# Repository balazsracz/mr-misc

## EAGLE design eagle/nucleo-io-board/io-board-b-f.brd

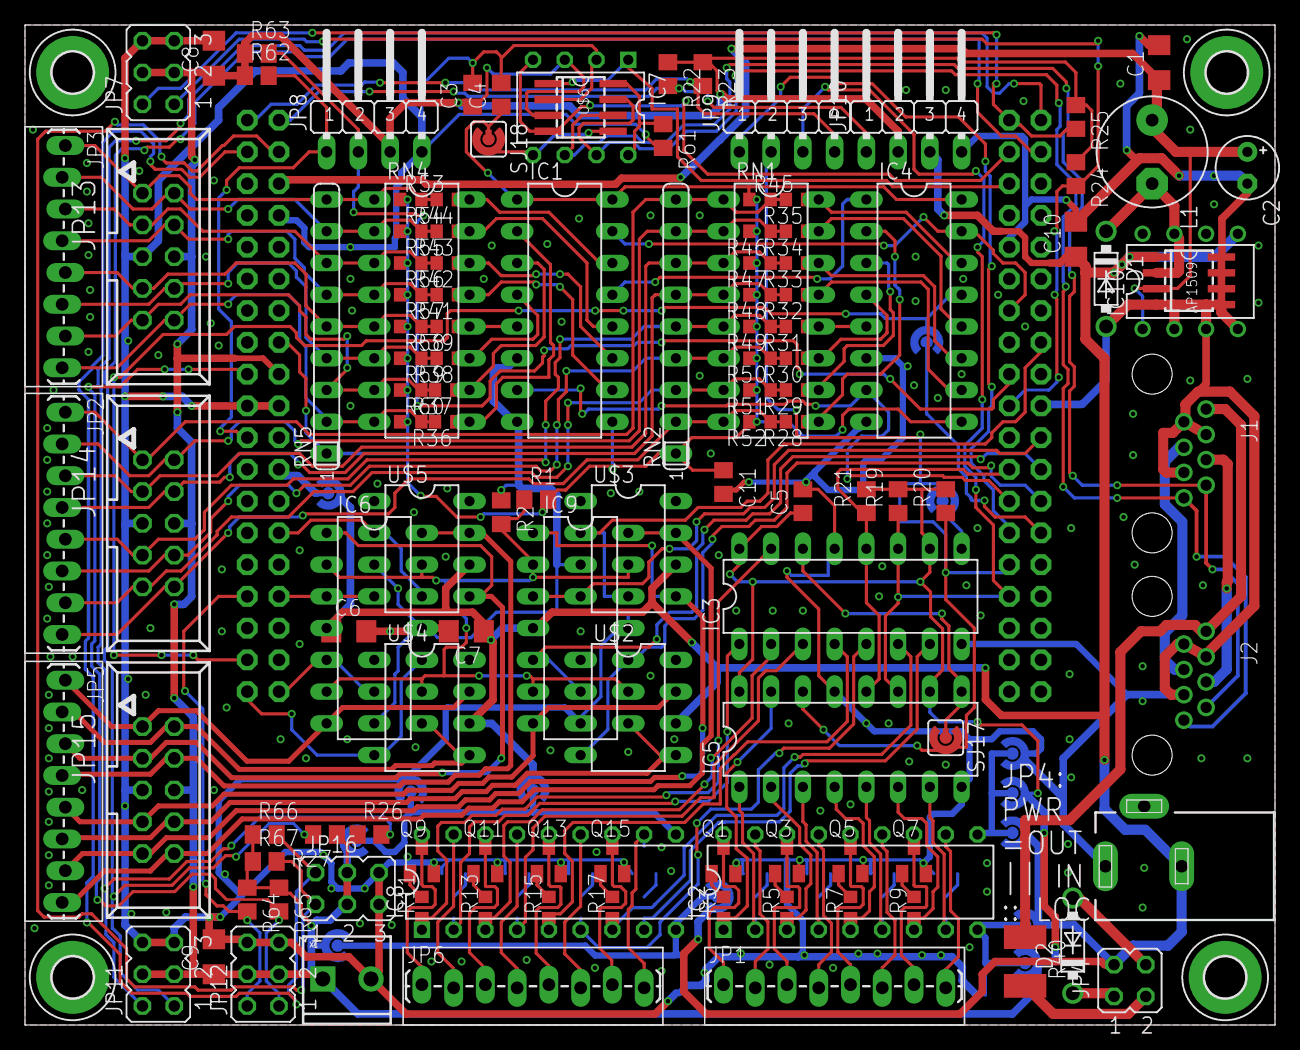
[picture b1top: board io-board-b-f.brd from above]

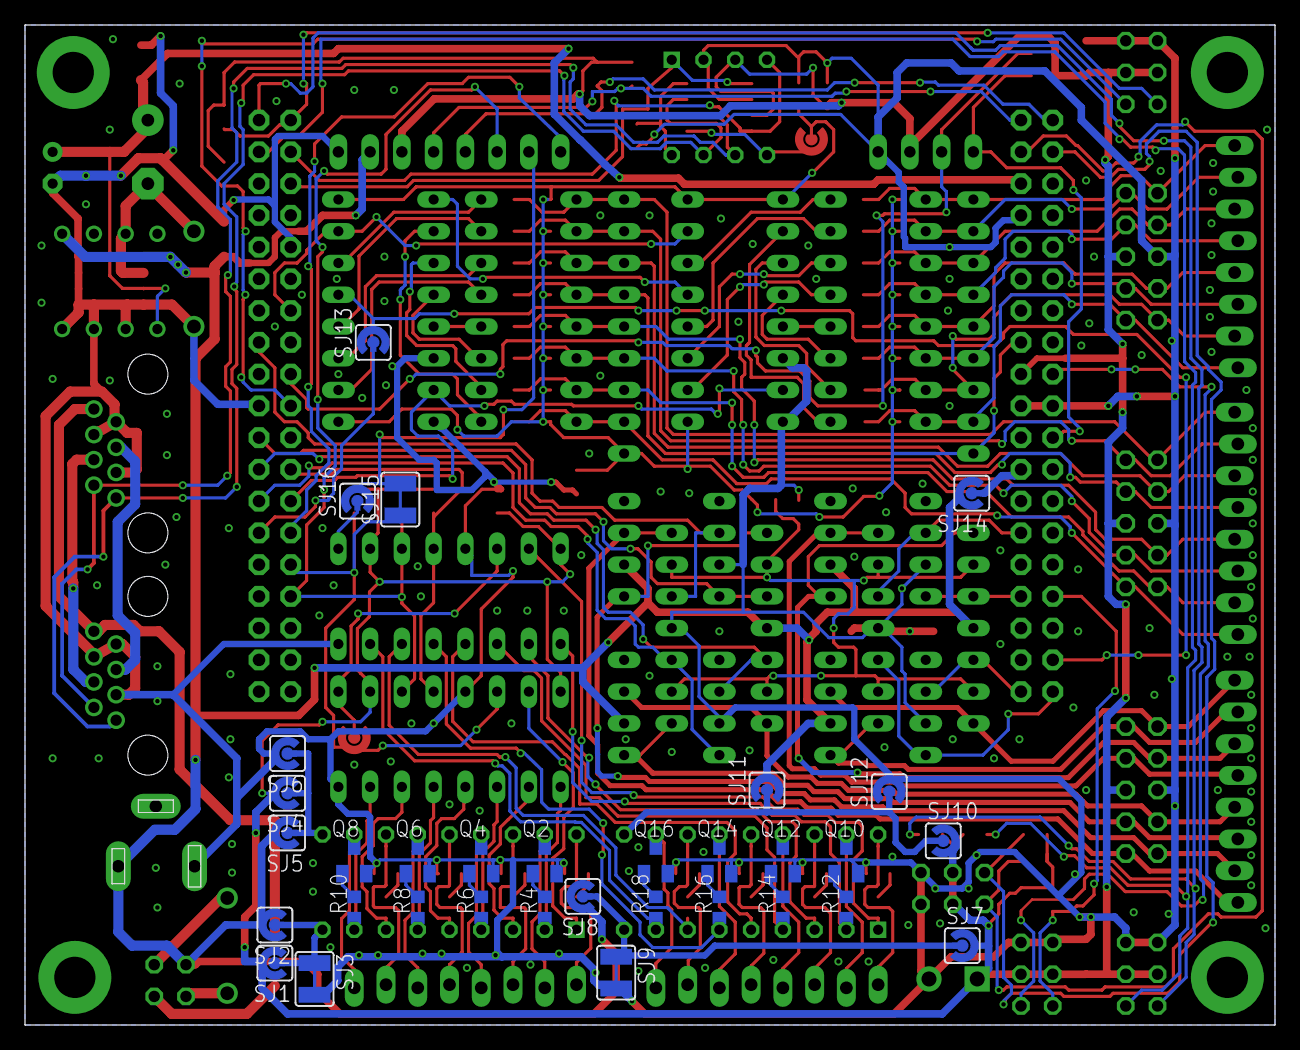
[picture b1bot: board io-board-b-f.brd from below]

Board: 2 copper layers, 100.0 x 80.0 mm, 161 parts (32 on the bottom side), 144 nets.

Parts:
+12V: 9-15V; POWER_USAGE
AP1509: AP1509; SO-08
C1, C6, C7, C8, C9, C10: C1206
C2: E2,5-5
C3, C4, C5, C11: C0805
D1, D2: DO41-7.6
H1, H2, H3, H4: MOUNT-PAD-ROUND3.3; 3,3-PAD
IC1, IC4: 74166N; DIL16
IC2, IC8: DIL18-THIN
IC3, IC5: 74HCT595N; DIL16
IC6, IC9: LM324N; DIL14
IC7: PCA82C250; DIL08
IC10: LM2574N-5.0; DIL08
J1, J2: RJ45-JACKRJ45-PULSE-E5J00; RJ45-PULSE-E5J88
J3: DCJ0202
JP1, JP2, JP3, JP5, JP6: M08-SCREW; 1X08_TERMINAL
JP4: JP2Q
JP7, JP11, JP12, JP16: JP3Q
JP8, JP9, JP10: JP4F
JP13, JP14, JP15: CON10M
L1: L-US; L5-8,5
Q1, Q2, Q3, Q4, Q5, Q6, Q7, Q8, Q9, Q10, Q11, Q12, Q13, Q14, Q15, Q16: SOT23
R1, R2: 10k; R0805
R3, R4, R5, R6, R7, R8, R9, R10, R11, R12, R13, R14, R15, R16, R17, R18, R28, R29, R30, R31, R32, R33, R34, R35, R36, R37, R38, R39, R41, R42, R43, R44, R45, R46, R47, R48, R49, R50, R51, R52, R53, R54, R55, R56, R57, R58, R59, R60: R0603
R19, R20, R21, R22, R23, R24, R25, R26, R27, R61, R62, R63, R64, R65, R66, R67: R0805
R40: 0ZCG0035AF2C; PTC1812
RN1, RN4: DIL16
RN2, RN5: 10K; SIL9
SJ1, SJ2, SJ4, SJ5, SJ6, SJ7, SJ8, SJ10, SJ11, SJ12, SJ13, SJ14, SJ16, SJ17, SJ18: SJ_RND2
SJ3, SJ9, SJ15: SJW-C
U$1: NUCLEO_64_GENERIC; NUCLEO_BRD_BASE64
U$2, U$3, U$4, U$5: TC4426APDIP; DIL08-LONG
U$6: MCP2551-SN; SO-08
X1: SCREWTERMINAL-3.5MM-2_LOCK

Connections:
+3.3V: C4.1, C11.1, IC1.1, IC1.9, IC1.16, IC4.9, IC4.16, R1.2, R45.1, R46.2, R47.2, R48.2, R49.2, R50.2, R51.2, R52.2, R53.1, R54.1, R55.1, R56.1, R57.1, R58.1, R59.1, R60.1, RN2.1, RN5.1, SJ18.P$1, U$1.3V3
+5V: C3.1, C5.1, C8.1, C9.1, IC3.10, IC3.16, IC5.10, IC5.16, IC7.3, JP7.3, JP7.4, JP8.3, JP10.2, JP11.3, JP11.4, JP12.3, JP12.4, JP13.6, JP14.6, JP15.6, JP16.3, JP16.4, R19.2, R20.2, R21.2, R22.1, R23.1, R24.1, R25.1, R26.1, R27.1, R62.1, R63.1, R64.1, R65.1, R66.1, R67.1, SJ1.P$2, SJ4.P$2, SJ7.P$2, SJ10.P$2, U$1.5V2, U$6.3, X1.1
+12V: AP1509.1, C6.1, C7.1, C10.1, IC6.4, IC9.4, IC10.5, J3.3, JP4.2, JP10.3, SJ2.P$2, SJ5.P$2, SJ8.P$2, SJ11.P$2, SJ14.P$2, U$2.6, U$3.6, U$4.6, U$5.6
CANH: IC7.7, J1.1, J2.1, U$6.7
CANL: IC7.6, J1.2, J2.2, U$6.6
CANRX: IC7.4, U$1.PB8, U$6.4
CANTX: IC7.1, U$1.PB9, U$6.1
CAN_RS: IC7.8, R61.1, U$6.8
CAN_VIO: IC7.5, SJ18.P$2, U$6.5
CMPREF: IC6.2, IC6.6, IC6.9, IC6.13, IC9.2, IC9.6, IC9.9, IC9.13, R1.1, R2.2
E_CS: JP9.4, R23.2, U$1.PC10
E_LAT: JP10.1, R22.2, U$1.PC11
E_MOSI: JP9.2, SJ15.2, SJ16.P$2
GND: AP1509.4, AP1509.5, AP1509.6, AP1509.7, AP1509.8, C1.2, C2.-, C3.2, C4.2, C5.2, C6.2, C7.2, C8.2, C9.2, C10.2, C11.2, D1.A, IC1.6, IC1.8, IC3.8, IC3.13, IC4.6, IC4.8, IC5.8, IC5.13, IC6.11, IC7.2, IC9.11, IC10.2, IC10.3, IC10.4, J1.3, J1.6, J1.7, J2.3, J2.6, J2.7, J3.1, JP7.5, JP7.6, JP8.4, JP10.4, JP11.5, JP11.6, JP12.5, JP12.6, JP13.5, JP14.5, JP15.5, JP16.5, JP16.6, Q1.2, Q2.2, Q3.2, Q4.2, Q5.2, Q6.2, Q7.2, Q8.2, Q9.2, Q10.2, Q11.2, Q12.2, Q13.2, Q14.2, Q15.2, Q16.2, R2.1, R61.2, SJ3.2, SJ6.P$2, SJ9.2, SJ12.P$2, U$1.GND3, U$1.GND5, U$1.GND6, U$1.GND7, U$1.GND8, U$2.3, U$3.3, U$4.3, U$5.3, U$6.2, X1.2
I2CSCL: JP8.2, R63.2, U$1.PB6
I2CSDA: JP8.1, R62.2, U$1.PB7
ILAT: IC1.15, IC4.15, U$1.PA6
LPOWA: IC8.9, SJ7.P$1, SJ8.P$1, SJ9.1
LPOWB: IC8.10, SJ10.P$1, SJ11.P$1, SJ12.P$1
MISO: JP9.1, U$1.PB4
MISO2: IC4.13, SJ13.P$2, U$1.PC2
MISO2_ALT: SJ13.P$1, U$1.PB14
MOSI: IC5.14, R20.1, SJ15.1, SJ17.P$2, U$1.PB5
unnamed: IC2.1, IC5.15, R3.1
unnamed: IC2.18, JP1.1, Q1.3
unnamed: IC2.2, IC5.1, R4.1
unnamed: J1.4, J2.4
unnamed: J1.5, J2.5
unnamed: JP3.8, JP13.10, R36.2, R60.2, RN4.8, RN5.2
unnamed: IC2.17, JP1.2, Q2.3
unnamed: IC2.3, IC5.2, R5.1
unnamed: IC2.16, JP1.3, Q3.3
unnamed: IC2.4, IC5.3, R6.1
unnamed: IC2.15, JP1.4, Q4.3
unnamed: IC2.5, IC5.4, R7.1
unnamed: IC2.14, JP1.5, Q5.3
unnamed: JP3.7, JP13.9, R37.2, R59.2, RN4.7, RN5.3
unnamed: JP3.6, JP13.8, R38.2, R58.2, RN4.6, RN5.4
unnamed: Q4.1, R6.2
unnamed: IC2.6, IC5.5, R8.1
unnamed: IC2.13, JP1.6, Q6.3
unnamed: JP3.4, JP13.4, R41.2, R56.2, RN4.4, RN5.6
unnamed: JP3.3, JP13.3, R42.2, R55.2, RN4.3, RN5.7
unnamed: JP2.6, JP14.8, R30.2, R50.1, RN1.6, RN2.4
unnamed: JP3.1, JP13.1, R44.2, R53.2, RN4.1, RN5.9
unnamed: IC1.2, R36.1, RN4.9
unnamed: IC1.3, R37.1, RN4.10
unnamed: JP2.8, JP14.10, R28.2, R52.1, RN1.8, RN2.2
unnamed: JP2.7, JP14.9, R29.2, R51.1, RN1.7, RN2.3
unnamed: Q5.1, R7.2
unnamed: JP2.5, JP14.7, R31.2, R49.1, RN1.5, RN2.5
unnamed: IC1.4, R38.1, RN4.11
unnamed: IC1.5, R39.1, RN4.12
unnamed: IC1.10, R41.1, RN4.13
unnamed: IC1.11, R42.1, RN4.14
unnamed: JP2.4, JP14.4, R32.2, R48.1, RN1.4, RN2.6
unnamed: JP2.3, JP14.3, R33.2, R47.1, RN1.3, RN2.7
unnamed: JP2.2, JP14.2, R34.2, R46.1, RN1.2, RN2.8
unnamed: JP2.1, JP14.1, R35.2, R45.2, RN1.1, RN2.9
unnamed: IC1.12, R43.1, RN4.15
unnamed: IC1.14, R44.1, RN4.16
unnamed: IC2.7, IC5.6, R9.1
unnamed: IC2.12, JP1.7, Q7.3
unnamed: IC2.8, IC5.7, R10.1
unnamed: IC2.11, JP1.8, Q8.3
unnamed: Q6.1, R8.2
unnamed: IC4.2, R28.1, RN1.9
unnamed: D2.C, JP4.1
unnamed: D2.A, JP4.4
unnamed: IC4.3, R29.1, RN1.10
unnamed: IC4.4, R30.1, RN1.11
unnamed: IC4.5, R31.1, RN1.12
unnamed: IC4.10, R32.1, RN1.13
unnamed: IC4.11, R33.1, RN1.14
unnamed: IC4.12, R34.1, RN1.15
unnamed: IC4.14, R35.1, RN1.16
unnamed: IC3.15, IC8.1, R11.1
unnamed: JP4.3, R40.2
unnamed: SJ14.P$1, U$1.VIN2
unnamed: Q7.1, R9.2
unnamed: IC8.11, JP6.8, Q16.3
unnamed: Q1.1, R3.2
unnamed: Q2.1, R4.2
unnamed: JP3.5, JP13.7, R39.2, R57.2, RN4.5, RN5.5
unnamed: JP3.2, JP13.2, R43.2, R54.2, RN4.2, RN5.8
unnamed: Q8.1, R10.2
unnamed: IC8.18, JP6.1, Q9.3
unnamed: Q3.1, R5.2
unnamed: IC3.1, IC8.2, R12.1
unnamed: IC8.17, JP6.2, Q10.3
unnamed: IC3.2, IC8.3, R13.1
unnamed: IC8.16, JP6.3, Q11.3
unnamed: IC3.3, IC8.4, R14.1
unnamed: IC8.15, JP6.4, Q12.3
unnamed: IC3.4, IC8.5, R15.1
unnamed: IC8.14, JP6.5, Q13.3
unnamed: IC3.5, IC8.6, R16.1
unnamed: IC8.13, JP6.6, Q14.3
unnamed: IC3.6, IC8.7, R17.1
unnamed: IC8.12, JP6.7, Q15.3
unnamed: IC3.7, IC8.8, R18.1
unnamed: Q9.1, R11.2
unnamed: Q10.1, R12.2
unnamed: Q11.1, R13.2
unnamed: Q12.1, R14.2
unnamed: Q13.1, R15.2
unnamed: Q14.1, R16.2
unnamed: Q15.1, R17.2
unnamed: Q16.1, R18.2
OLAT: IC3.12, IC5.12, R21.1, U$1.PA8
PWR_POS: J1.8, J2.8, R40.1
RPOWA: IC2.9, SJ1.P$1, SJ2.P$1, SJ3.1
RPOWB: IC2.10, SJ4.P$1, SJ5.P$1, SJ6.P$1
SCK: IC3.11, IC5.11, JP9.3, R19.1, U$1.PB3
SCK2: IC1.7, IC4.7, U$1.PB10
SLNK1: IC3.14, IC5.9, SJ17.P$1
SLNK2: IC3.9, SJ16.P$1
SLNK3: IC1.13, IC4.1
SRV1: JP7.2, R25.2, U$1.PC9
SRV2: JP7.1, R24.2, U$1.PC7
SRV3: JP11.2, R26.2, U$1.PC8
SRV4: JP11.1, R27.2, U$1.PC6
SRV5: JP12.2, R64.2, U$1.PF1-PH1
SRV6: JP12.1, R65.2, U$1.PA15
SRV7: JP16.2, R66.2, U$1.PC12
SRV8: JP16.1, R67.2, U$1.PD2
SW: AP1509.2, D1.C, IC10.7, L1.2
TIN1: IC9.3, U$1.PB2, U$3.4
TIN2: IC9.5, U$1.PB1, U$2.2
TIN3: IC9.10, U$1.PB15, U$2.4
TIN4: IC9.12, U$1.PB12, U$3.2
TIN5: IC6.3, U$1.PA4, U$5.4
TIN6: IC6.5, U$1.PC0, U$4.2
TIN7: IC6.10, U$1.PC3, U$4.4
TIN8: IC6.12, U$1.PA0, U$5.2
TOUT1: IC6.7, JP5.1, JP15.1, U$4.7
TOUT2: IC6.8, JP5.2, JP15.2, U$4.5
TOUT3: IC6.1, JP5.3, JP15.3, U$5.5
TOUT4: IC6.14, JP5.4, JP15.4, U$5.7
TOUT5: IC9.7, JP5.5, JP15.7, U$2.7
TOUT6: IC9.8, JP5.6, JP15.8, U$2.5
TOUT7: IC9.1, JP5.7, JP15.9, U$3.5
TOUT8: IC9.14, JP5.8, JP15.10, U$3.7
V+: AP1509.3, C1.1, C2.+, IC10.1, L1.1, U$1.E5V
